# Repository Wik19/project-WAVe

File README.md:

# project-WAVe: Vibroacoustic Measurement System for Flapping-Wing Drones

## Overview
**project-WAVe** (Wing Acoustic & Vibroacoustic Experiment) is a custom wireless measurement system designed for flapping-wing drones. This repository contains the hardware design, firmware, and software for a high-fidelity data acquisition platform, specifically tailored as a lightweight expansion deck for the [Flapper Nimble+](https://flapper-drones.com/product/flapper-nimble/) platform.

It serves as a foundation for collecting large-scale vibroacoustic datasets required to develop future machine learning-based Fault Detection and Diagnosis (FDD) algorithms.

## Key Features
* **Miniaturized Custom Hardware**: A custom 4-layer PCB (25.2 x 27.3 mm) designed to fit the standard Bitcraze Crazyflie expansion deck footprint.
* **High-Fidelity Inertial Tracking**: LSM6DS3TR-C 6-DOF IMU capturing 3-axis acceleration and angular velocity via SPI.
* **Precision Acoustic Acquisition**: INMP441 digital MEMS microphone via I2S for 24-bit resolution acoustic recordings.
* **Real-Time Wireless Streaming**: ESP32-C3 microcontroller actings as a TCP server, streaming data over 2.45 GHz Wi-Fi.
* **Concurrent Processing**: Efficient use of DMA, dual-buffers, and hardware interrupts for simultaneous data collection and transmission.

## Repository Structure
The project is organized into three technical domains:

### [WAVe-PCB](./WAVe-PCB)
Contains the electronics design files (KiCad).
* **MCU**: ESP32-C3FH4 SoC.
* **Sensors**: LSM6DS3TR-C IMU & INMP441 Microphone.
* **Power**: TPS566238RQFR buck converter for stable 3.3V delivery.

### [data-collection](./data-collection)
Embedded firmware developed using PlatformIO and the ESP-IDF framework.
* Manages low-level task scheduling (FreeRTOS).
* Handles interrupt-driven sensor readings and network transmission.
* Optimized for high-frequency IMU and acoustic data streaming.

### [data-processing](./data-processing)
Python client for real-time data reception and analysis.
* Utilizes TCP sockets to receive high-bandwidth data frames.
* Implements SciPy for real-time parsing, FFT, and STFT spectrogram visualizations.
* Specifically adapted for capturing 3-second IMU frames for diagnostic analysis.

## Experimental Validation
The system has been successfully validated through:
1. **Bench Testing**: Verification of sensor fidelity and wireless throughput.
2. **In-Flight Trials**: Successful capture of distinct cyclostationary vibroacoustic signatures during hover and forward flight maneuvers.
3. **Decoupled Architecture**: High-bandwidth data handling without introducing latency to the drone's primary flight controller.

## Authors
* [Marco Wiktor Santoro](https://github.com/Wik19)
* [Olaf Bukowski](https://github.com/olaf-bukowski)

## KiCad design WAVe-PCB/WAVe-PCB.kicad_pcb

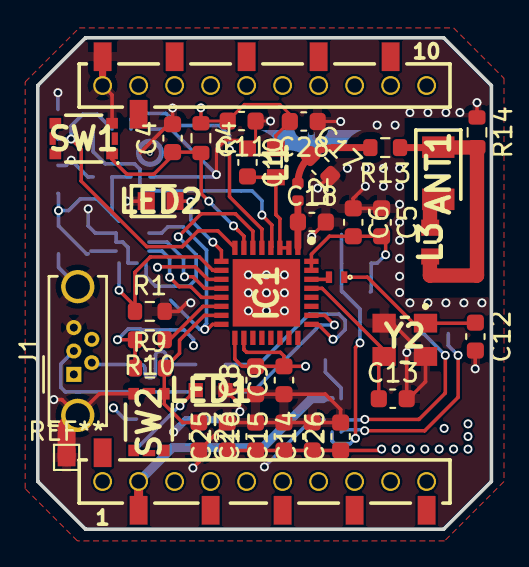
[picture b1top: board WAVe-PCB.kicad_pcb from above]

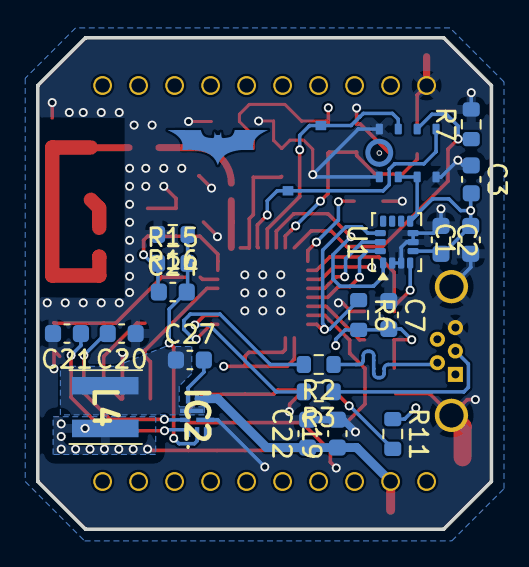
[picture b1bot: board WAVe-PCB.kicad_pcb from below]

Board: 4 copper layers, 25.2 x 27.3 mm, 58 parts (21 on the bottom side), 33 nets.

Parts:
ANT1: 2450AT18E0100E; ANTC3216X130N
C1, C2, C3, C4, C7, C8, C9, C11, C22, C23, C26, C27: 100n; C_0603_1608Metric
C5, C20: 10n; C_0603_1608Metric
C6, C10, C21: 1u; C_0603_1608Metric
C12, C13, C17, C18: TBD; C_0603_1608Metric
C14, C15, C16: 22u; C_0603_1608Metric
C19: 47u; C_0603_1608Metric
C24: 33p; C_0603_1608Metric
C25: 4x 22u; C_0603_1608Metric
C28: 10u; C_0603_1608Metric
IC1: ESP32-C3FH4; QFN50P500X500X90-33N-D
IC2: TPS566238RQFR
J1: USB_Micro-B_Wuerth_614105150721_Vertical_Circular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; USB_Micro-B_Wuerth_614105150721_Vertical_CircularHoles
L1: 2n; INDC1608X95N
L2: TBD; L_0402_1005Metric
L3: 1n2; INDC1608X95N
L4: 1.5u; 74438357015
LED1: APT1608LSECK_J3-PRV; APT1608CGCK
LED2: 150060GS83000; LEDC1608X115N
P1: CF_EXP; drone_connector
R1, R4, R6, R9, R10, R11: 10k; R_0603_1608Metric
R2, R3: 22; R_0603_1608Metric
R5: 24nH; MHQ1005
R7: 100k; R_0603_1608Metric
R13, R14: 0R; R_0603_1608Metric
R15: 90k9; R_0603_1608Metric
R16: 20k; R_0603_1608Metric
SW1, SW2: SW_Push; 435151014824
U1: LSM6DS3; LGA-14_3x2.5mm_P0.5mm_LayoutBorder3x4y
U2: INMP441
Y2: ABM8-40.000MHZ-B2-T; ABM810000MHZ12D2W

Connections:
+3V3: C1.2, C2.2, C3.2, C5.2, C6.2, C7.2, C8.2, C9.2, C11.2, C14.1, C15.1, C16.1, C24.1, C25.1, C26.1, C28.2, IC1.11 (VDD3P3_RTC), IC1.17 (VDD3P3_CPU), IC1.18 (VDD_SPI), IC1.31 (VDDA_1), IC1.32 (VDDA_2), L1.1, L4.2, R4.1, R6.2, R9.1, R10.2, R11.1, R15.1, U1.5 (VDDIO), U1.8 (VDD), U2.7 (VCC), U2.8 (EN)
+BATT: C19.1, C22.1, IC2.5 (VIN_1), IC2.6 (VIN_2), P1.19 (VCOM)
/BOOT: C23.1, IC1.15 (GPIO9), R9.2, SW2.1
/CS: IC1.16 (GPIO10), R6.1, U1.12 (CS)
/DO: IC1.6 (GPIO2), U1.1 (SDO/SA0)
/LED_G: IC1.9 (MTMS), LED2.2 (A)
/RESET: C4.1, IC1.7 (CHIP_EN), R4.2, SW1.1
/SCK: IC1.4 (XTAL_32K_P), U2.1 (SCK)
/SCL: IC1.12 (MTCK), U1.13 (SCL)
/SD: IC1.8 (GPIO3), R7.1, U2.2 (SD)
/SDA: IC1.13 (MTDO), U1.14 (SDA)
/USB_D+: IC1.26 (GPIO19), R3.2
/USB_D-: IC1.25 (GPIO18), R2.2
/WS: IC1.5 (XTAL_32K_N), U2.3 (WS)
/antenna: C18.1, IC1.1 (LNA_IN), L2.2
/int1: IC1.10 (MTDI), R1.1, U1.4 (INT1)
/xtal_1: C12.1, R5.1, Y2.1 (X1)
/xtal_2: C13.1, IC1.29 (XTAL_N), Y2.3 (X2)
GND: C1.1, C2.1, C3.1, C4.2, C5.1, C6.1, C7.1, C8.1, C9.1, C10.1, C11.1, C12.2, C13.2, C14.2, C15.2, C16.2, C17.2, C18.2, C19.2, C20.1, C21.2, C22.2, C23.2, C25.2, C26.2, C28.1, IC1.33 (EP), IC2.4 (PGND), J1.5, J1.6, LED1.1 (K), LED2.1 (K), P1.10 (GND), R1.2, R7.2, R14.1, R16.2, SW1.3, SW2.3, U1.2 (SDX), U1.3 (SCX), U1.6 (GND), U1.7 (GND), U2.4 (L/R), U2.6 (GND), U2.9 (GND), Y2.2 (GND_1), Y2.4 (GND_2)
unnamed: ANT1.1 (FEED), L3.2, R13.1, R14.2
unnamed: ANT1.2 (NC), L3.1
unnamed: C17.1, L2.1, R13.2
unnamed: IC1.14 (GPIO8), R10.1
unnamed: C10.2, IC1.2 (VDD3P3_1), IC1.3 (VDD3P3_2), L1.2
unnamed: IC1.30 (XTAL_P), R5.2
unnamed: C27.2, IC2.7 (BST)
unnamed: C24.2, IC2.2 (FB), R15.2, R16.1
unnamed: C20.2, IC2.9 (SS)
unnamed: C27.1, IC2.8 (SW), L4.1
unnamed: C21.1, IC2.1 (VCC)
unnamed: J1.2, R2.1
unnamed: J1.3, R3.1
unnamed: LED1.2 (A), R11.2

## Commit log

2025-11-07 added new microphone
2025-11-07 finish connecting, add decoupling capacitors on pcb
2025-11-07 changed name of project, fixed main issues, waiting for final confirmation
2025-11-10 added mcu led & minor adjustments
2025-11-11 Naprawa przetwornicy zasilajacej, dodanie rezystorow na linie D+ D-, ogolna naprawa polaczen na plytce i debug
2025-11-11 adjustments
2025-12-23 fix ESP code, starting circuit redesign
2025-12-23 finish organizing the new connections between sub-schematics
2025-12-25 connected hierarchical schematics
2025-12-25 replaced new mic with old mic (INMP441)
2026-01-04 split main.c file into multiple, organized, files. Can't check if they work on the board yet
2026-01-07 works!
2026-01-12 python script adapted to capturing 3s imu frames from current .c code
2026-01-18 We created a full standalone dual sensor capturing system, however it still requires some cleanup and arrangement
2026-01-22 complete project, only post-processing to improve
2026-03-13 Add README for project-WAVe description and features
